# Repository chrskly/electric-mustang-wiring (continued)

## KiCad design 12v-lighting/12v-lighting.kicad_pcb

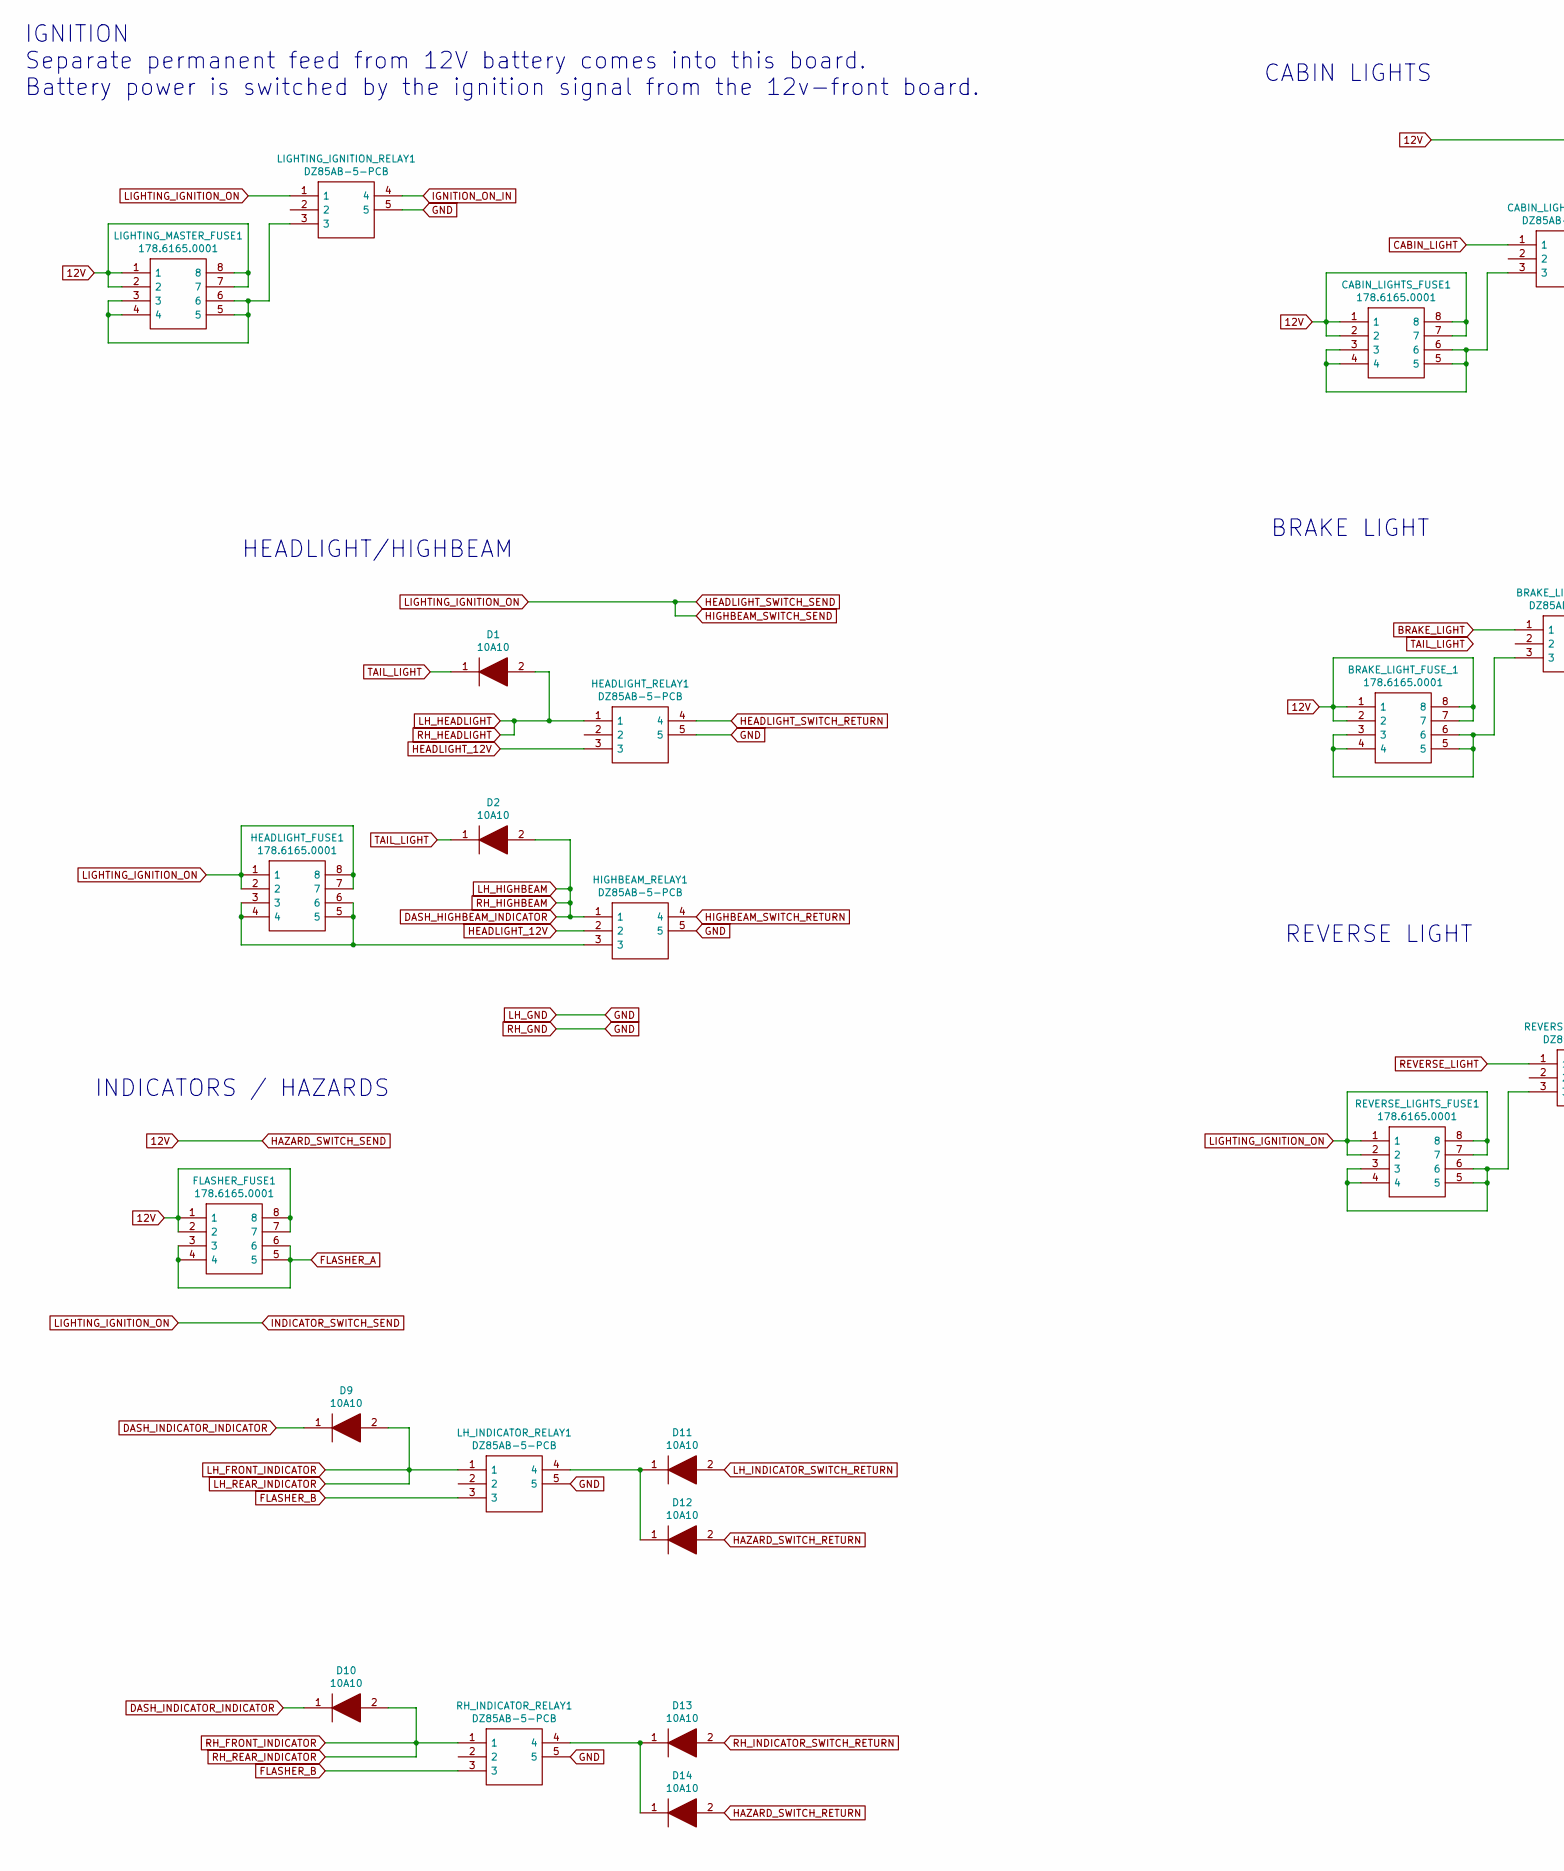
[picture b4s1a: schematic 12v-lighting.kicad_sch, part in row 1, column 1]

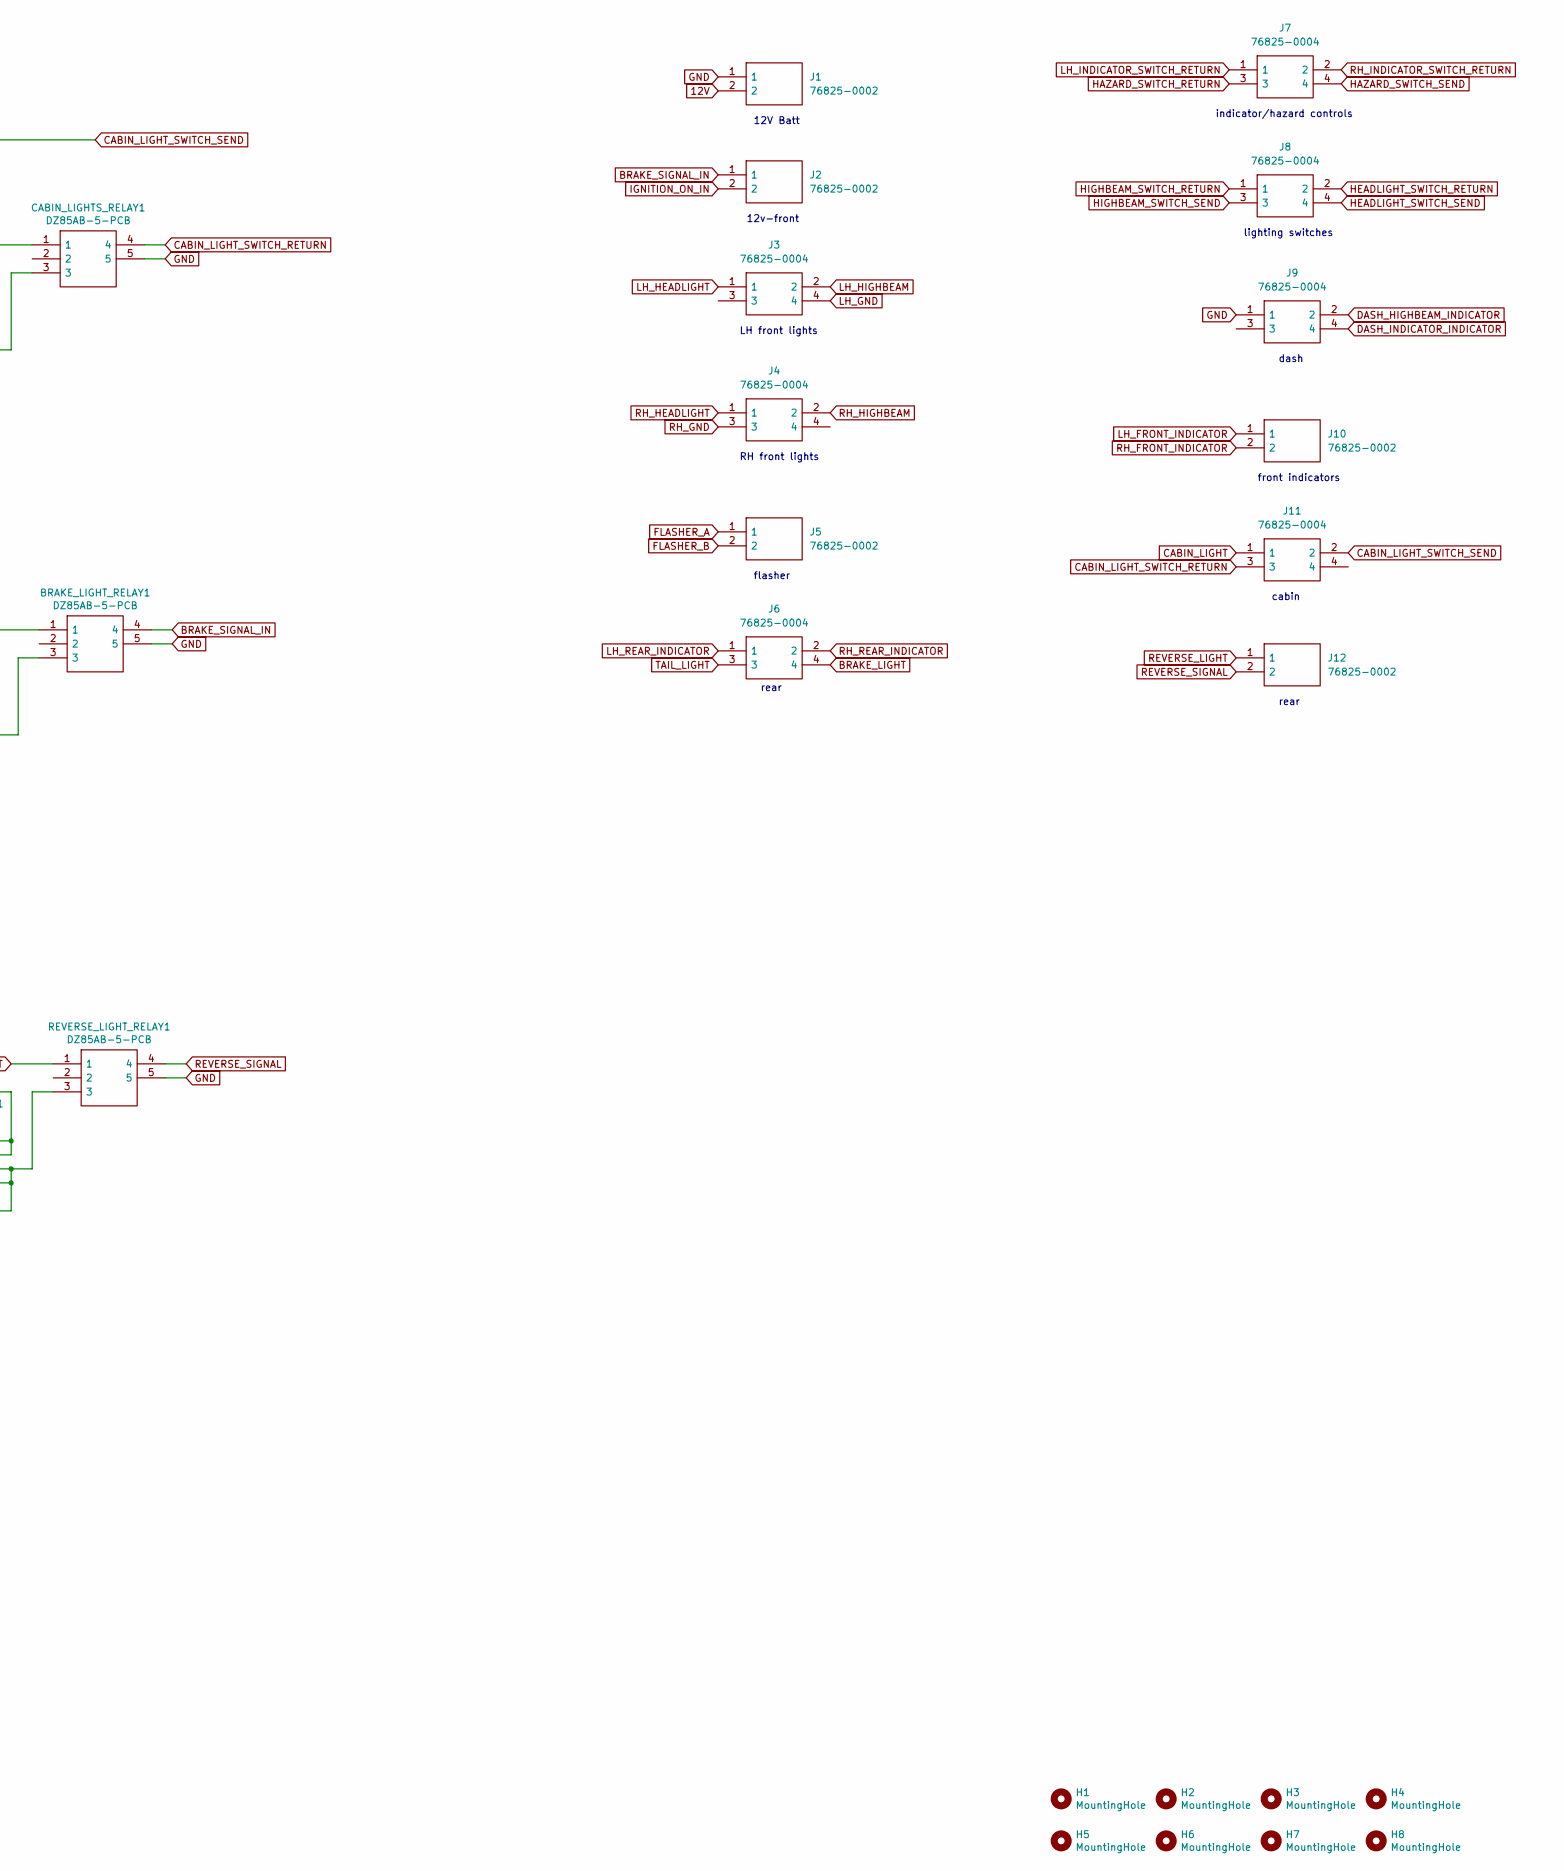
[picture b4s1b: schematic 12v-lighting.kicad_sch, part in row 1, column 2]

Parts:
BRAKE_LIGHT_FUSE_1: 178.6165.0001; 17861650001; Manufacturer_Part_Number 178.6165.0001; Mouser Part Number 576-178.6165.0001
BRAKE_LIGHT_RELAY1: DZ85AB-5-PCB; DZ85AB5PCB; Manufacturer_Part_Number DZ85AB-5-PCB
CABIN_LIGHTS_FUSE1: 178.6165.0001; 17861650001; Manufacturer_Part_Number 178.6165.0001; Mouser Part Number 576-178.6165.0001
CABIN_LIGHTS_RELAY1: DZ85AB-5-PCB; DZ85AB5PCB; Manufacturer_Part_Number DZ85AB-5-PCB
D1, D2, D9, D10, D11, D12, D13, D14: 10A10; D_DO-201AD_P15.24mm_Horizontal; Manufacturer_Part_Number 10A10
FLASHER_FUSE1: 178.6165.0001; 17861650001; Manufacturer_Part_Number 178.6165.0001; Mouser Part Number 576-178.6165.0001
H1, H2, H3, H4, H5, H6, H7, H8: MountingHole; MountingHole_3.2mm_M3
HEADLIGHT_FUSE1: 178.6165.0001; 17861650001; Manufacturer_Part_Number 178.6165.0001; Mouser Part Number 576-178.6165.0001
HEADLIGHT_RELAY1: DZ85AB-5-PCB; DZ85AB5PCB; Manufacturer_Part_Number DZ85AB-5-PCB
HIGHBEAM_RELAY1: DZ85AB-5-PCB; DZ85AB5PCB; Manufacturer_Part_Number DZ85AB-5-PCB
J1, J2, J5, J10, J12: 76825-0002; 768250002; Manufacturer_Part_Number 76825-0002; Mouser Part Number 538-76825-0002
J3, J4, J6, J7, J8, J9, J11: 76825-0004; 768250004; Manufacturer_Part_Number 76825-0004; Mouser Part Number 538-76825-0004
LH_INDICATOR_RELAY1: DZ85AB-5-PCB; DZ85AB5PCB; Manufacturer_Part_Number DZ85AB-5-PCB
LIGHTING_IGNITION_RELAY1: DZ85AB-5-PCB; DZ85AB5PCB; Manufacturer_Part_Number DZ85AB-5-PCB
LIGHTING_MASTER_FUSE1: 178.6165.0001; 17861650001; Manufacturer_Part_Number 178.6165.0001; Mouser Part Number 576-178.6165.0001
REVERSE_LIGHTS_FUSE1: 178.6165.0001; 17861650001; Manufacturer_Part_Number 178.6165.0001; Mouser Part Number 576-178.6165.0001
REVERSE_LIGHT_RELAY1: DZ85AB-5-PCB; DZ85AB5PCB; Manufacturer_Part_Number DZ85AB-5-PCB
RH_INDICATOR_RELAY1: DZ85AB-5-PCB; DZ85AB5PCB; Manufacturer_Part_Number DZ85AB-5-PCB

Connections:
12V: BRAKE_LIGHT_FUSE_1.1, BRAKE_LIGHT_FUSE_1.2, BRAKE_LIGHT_FUSE_1.7, BRAKE_LIGHT_FUSE_1.8, CABIN_LIGHTS_FUSE1.1, CABIN_LIGHTS_FUSE1.2, CABIN_LIGHTS_FUSE1.7, CABIN_LIGHTS_FUSE1.8, FLASHER_FUSE1.1, FLASHER_FUSE1.2, FLASHER_FUSE1.7, FLASHER_FUSE1.8, J1.2, J7.4, J11.2, LIGHTING_MASTER_FUSE1.1, LIGHTING_MASTER_FUSE1.2, LIGHTING_MASTER_FUSE1.7, LIGHTING_MASTER_FUSE1.8
BRAKE_LIGHT: BRAKE_LIGHT_RELAY1.1, J6.4
BRAKE_SIGNAL_IN: BRAKE_LIGHT_RELAY1.4, J2.1
CABIN_LIGHT: CABIN_LIGHTS_RELAY1.1, J11.1
CABIN_LIGHT_SWITCH_RETURN: CABIN_LIGHTS_RELAY1.4, J11.3
DASH_HIGHBEAM_INDICATOR: D2.2, HIGHBEAM_RELAY1.1, J3.2, J4.2, J9.2
DASH_INDICATOR_INDICATOR: D9.1, D10.1, J9.4
FLASHER_A: FLASHER_FUSE1.3, FLASHER_FUSE1.4, FLASHER_FUSE1.5, FLASHER_FUSE1.6, J5.1
FLASHER_B: J5.2, LH_INDICATOR_RELAY1.3, RH_INDICATOR_RELAY1.3
GND: BRAKE_LIGHT_RELAY1.5, CABIN_LIGHTS_RELAY1.5, HEADLIGHT_RELAY1.5, HIGHBEAM_RELAY1.5, J1.1, J3.4, J4.3, J9.1, LH_INDICATOR_RELAY1.5, LIGHTING_IGNITION_RELAY1.5, REVERSE_LIGHT_RELAY1.5, RH_INDICATOR_RELAY1.5
HAZARD_SWITCH_RETURN: D12.2, D14.2, J7.3
HEADLIGHT_12V: HEADLIGHT_RELAY1.3, HIGHBEAM_RELAY1.2
HEADLIGHT_SWITCH_RETURN: HEADLIGHT_RELAY1.4, J8.2
HEADLIGHT_SWITCH_SEND: HEADLIGHT_FUSE1.1, HEADLIGHT_FUSE1.2, HEADLIGHT_FUSE1.7, HEADLIGHT_FUSE1.8, J8.3, J8.4, LIGHTING_IGNITION_RELAY1.1, REVERSE_LIGHTS_FUSE1.1, REVERSE_LIGHTS_FUSE1.2, REVERSE_LIGHTS_FUSE1.7, REVERSE_LIGHTS_FUSE1.8
HIGHBEAM_SWITCH_RETURN: HIGHBEAM_RELAY1.4, J8.1
IGNITION_ON_IN: J2.2, LIGHTING_IGNITION_RELAY1.4
LH_FRONT_INDICATOR: D9.2, J6.1, J10.1, LH_INDICATOR_RELAY1.1
LH_HEADLIGHT: D1.2, HEADLIGHT_RELAY1.1, J3.1, J4.1
LH_INDICATOR_SWITCH_RETURN: D11.2, J7.1
unnamed: BRAKE_LIGHT_FUSE_1.3, BRAKE_LIGHT_FUSE_1.4, BRAKE_LIGHT_FUSE_1.5, BRAKE_LIGHT_FUSE_1.6, BRAKE_LIGHT_RELAY1.3
unnamed: CABIN_LIGHTS_FUSE1.3, CABIN_LIGHTS_FUSE1.4, CABIN_LIGHTS_FUSE1.5, CABIN_LIGHTS_FUSE1.6, CABIN_LIGHTS_RELAY1.3
unnamed: D11.1, D12.1, LH_INDICATOR_RELAY1.4
unnamed: D13.1, D14.1, RH_INDICATOR_RELAY1.4
unnamed: HEADLIGHT_FUSE1.3, HEADLIGHT_FUSE1.4, HEADLIGHT_FUSE1.5, HEADLIGHT_FUSE1.6, HIGHBEAM_RELAY1.3
unnamed: LIGHTING_IGNITION_RELAY1.3, LIGHTING_MASTER_FUSE1.3, LIGHTING_MASTER_FUSE1.4, LIGHTING_MASTER_FUSE1.5, LIGHTING_MASTER_FUSE1.6
unnamed: REVERSE_LIGHTS_FUSE1.3, REVERSE_LIGHTS_FUSE1.4, REVERSE_LIGHTS_FUSE1.5, REVERSE_LIGHTS_FUSE1.6, REVERSE_LIGHT_RELAY1.3
REVERSE_LIGHT: J12.1, REVERSE_LIGHT_RELAY1.1
REVERSE_SIGNAL: J12.2, REVERSE_LIGHT_RELAY1.4
RH_FRONT_INDICATOR: D10.2, J6.2, J10.2, RH_INDICATOR_RELAY1.1
RH_INDICATOR_SWITCH_RETURN: D13.2, J7.2
TAIL_LIGHT: D1.1, D2.1, J6.3

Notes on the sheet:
front indicators
lighting switches
RH front lights
12v-front
dash
LH front lights
REVERSE LIGHT
rear
HEADLIGHT/HIGHBEAM
CABIN LIGHTS
12V Batt
INDICATORS / HAZARDS
cabin
BRAKE LIGHT
flasher
IGNITION Separate permanent feed from 12V battery comes into this board. Battery power is switched by the ignition signal from the 12v-front board.
indicator/hazard controls

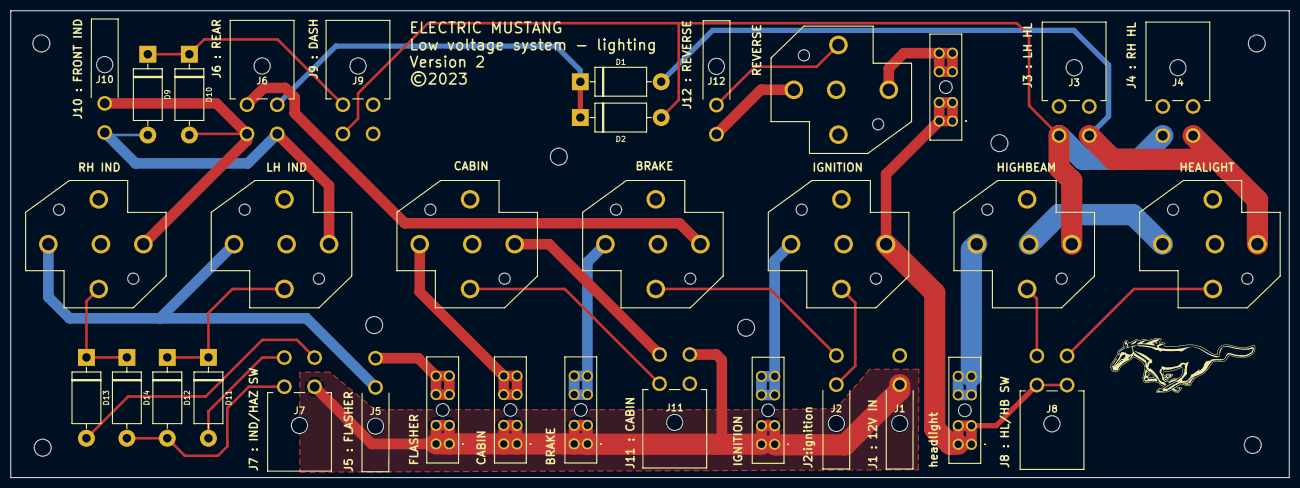
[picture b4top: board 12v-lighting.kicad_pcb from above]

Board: 2 copper layers, 241.0 x 88.0 mm, 42 parts (0 on the bottom side), 31 nets.

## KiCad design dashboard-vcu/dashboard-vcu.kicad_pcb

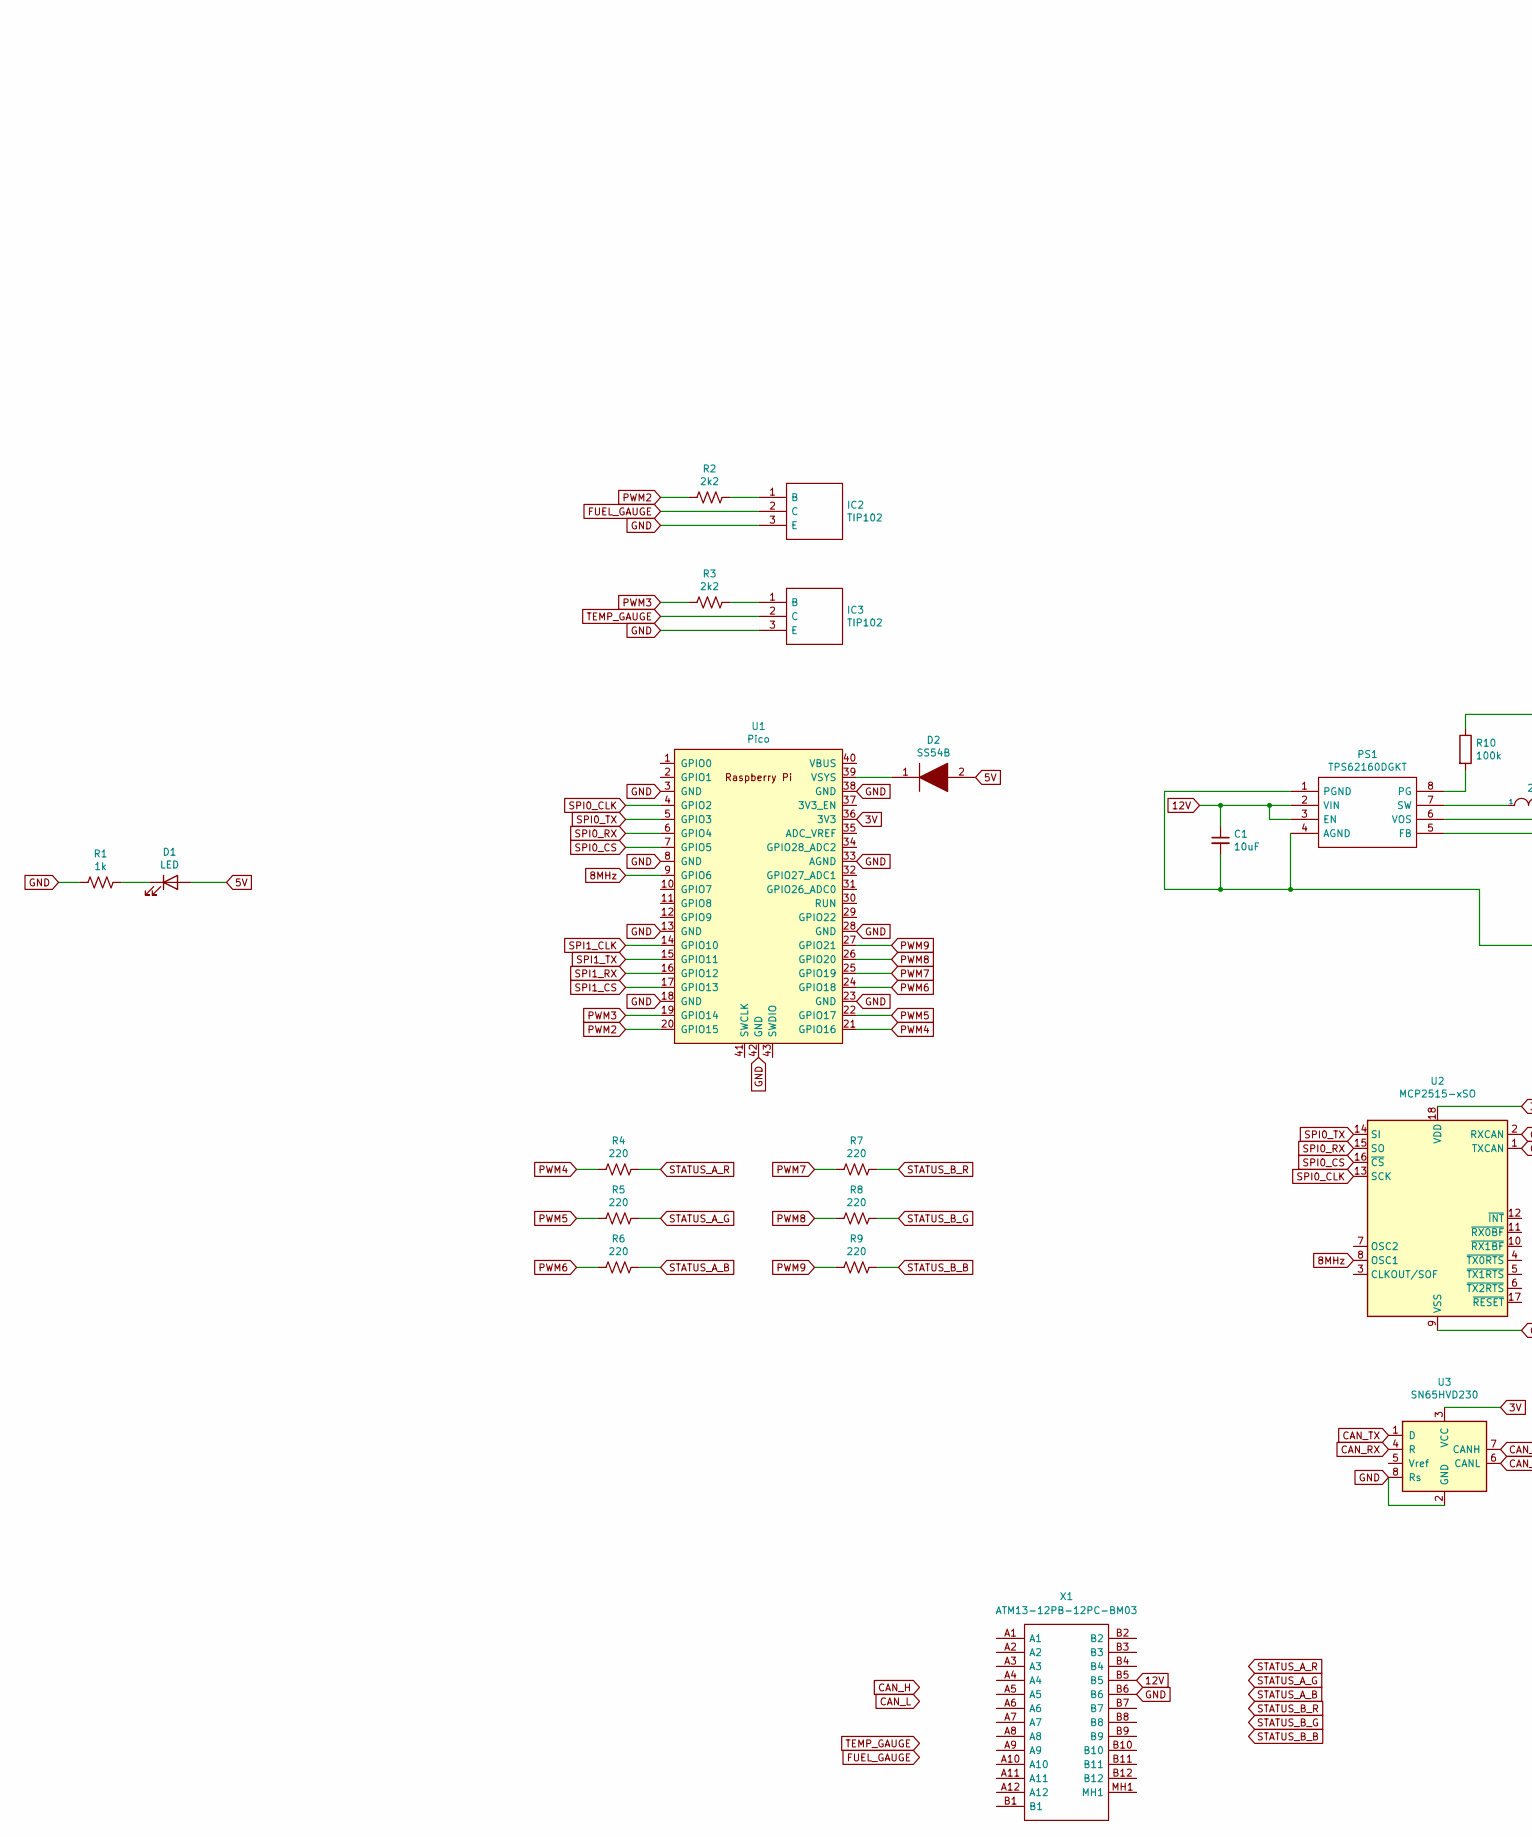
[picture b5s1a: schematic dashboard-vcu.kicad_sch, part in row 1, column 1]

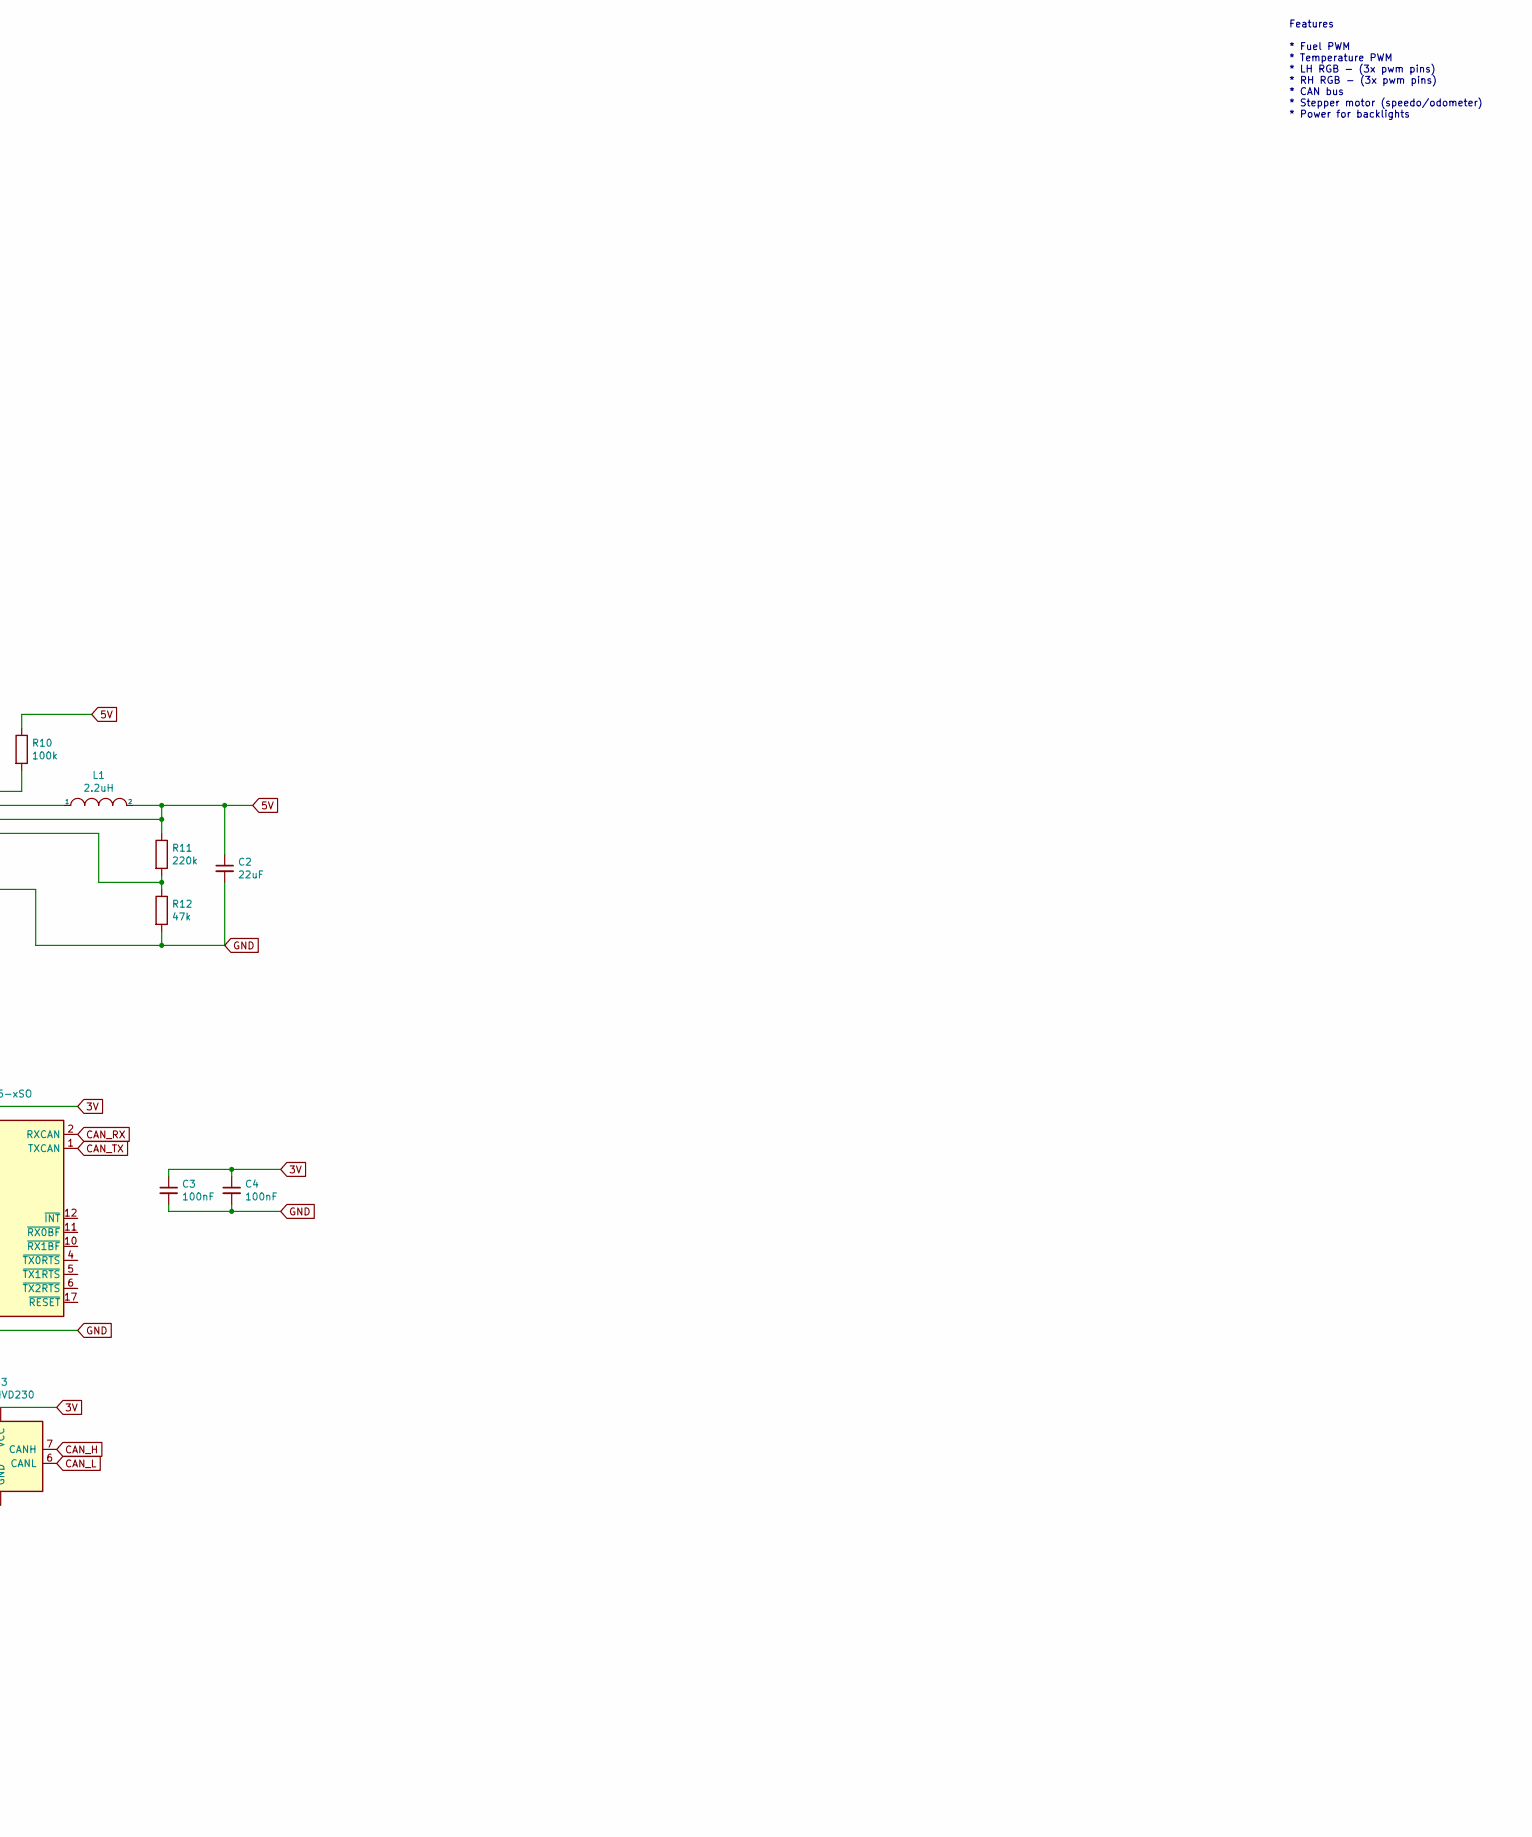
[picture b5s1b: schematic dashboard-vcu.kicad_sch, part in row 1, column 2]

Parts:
C1: 10uF; C_0603_1608Metric
C2: 22uF; C_0805_2012Metric
C3, C4: 100nF; C_0603_1608Metric
D1: LED; LED_0603_1608Metric
D2: SS54B; DIOM5336X244N; Manufacturer_Part_Number SS54B
IC2, IC3: TIP102; TO270P460X1020X2008-3P; Manufacturer_Part_Number TIP102; Mouser Part Number 511-TIP102
L1: 2.2uH; NR6028T220M
PS1: TPS62160DGKT; SOP65P490X110-8N; Manufacturer_Part_Number TPS62160DGKT; Mouser Part Number 595-TPS62160DGKT
R1: 1k; R_0201_0603Metric
R2, R3: 2k2; R_0201_0603Metric
R4, R5, R6, R7, R8, R9: 220; R_0201_0603Metric
R10: 100k; R_0201_0603Metric
R11: 220k; R_0201_0603Metric
R12: 47k; R_0201_0603Metric
U1: Pico; RPi_Pico_SMD_TH
U2: MCP2515-xSO; SOIC-18W_7.5x11.6mm_P1.27mm
U3: SN65HVD230; SOIC-8_3.9x4.9mm_P1.27mm
X1: ATM13-12PB-12PC-BM03; ATM1312PB12PCBM03; Manufacturer_Part_Number ATM13-12PB-12PC-BM03; Mouser Part Number 654-ATM1312B12PCBM03

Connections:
3V: C3.1, C4.1, U1.36 (3V3), U2.18 (VDD), U3.3 (VCC)
5V: C2.1, D1.2 (A), D2.2, L1.2, PS1.6 (VOS), R10.1, R11.1
8MHz: U1.9 (GPIO6), U2.8 (OSC1)
12V: C1.1, PS1.2 (VIN), PS1.3 (EN), X1.B5
CAN_H: U3.7 (CANH)
CAN_L: U3.6 (CANL)
CAN_RX: U2.2 (RXCAN), U3.4 (R)
CAN_TX: U2.1 (TXCAN), U3.1 (D)
FUEL_GAUGE: IC2.2 (C)
GND: C1.2, C2.2, C3.2, C4.2, IC2.3 (E), IC3.3 (E), PS1.1 (PGND), PS1.4 (AGND), R1.2, R12.2, U1.3 (GND), U1.8 (GND), U1.13 (GND), U1.18 (GND), U1.23 (GND), U1.28 (GND), U1.33 (AGND), U1.38 (GND), U1.42 (GND), U2.9 (VSS), U3.2 (GND), U3.8 (Rs), X1.B6
unnamed: D1.1 (K), R1.1
unnamed: D2.1, U1.39 (VSYS)
unnamed: IC2.1 (B), R2.1
unnamed: IC3.1 (B), R3.1
unnamed: L1.1, PS1.7 (SW)
unnamed: PS1.5 (FB), R11.2, R12.1
unnamed: PS1.8 (PG), R10.2
PWM2: R2.2, U1.20 (GPIO15)
PWM3: R3.2, U1.19 (GPIO14)
PWM4: R4.2, U1.21 (GPIO16)
PWM5: R5.2, U1.22 (GPIO17)
PWM6: R6.2, U1.24 (GPIO18)
PWM7: R7.2, U1.25 (GPIO19)
PWM8: R8.2, U1.26 (GPIO20)
PWM9: R9.2, U1.27 (GPIO21)
SPI0_CLK: U1.4 (GPIO2), U2.13 (SCK)
SPI0_CS: U1.7 (GPIO5), U2.16 (~CS)
SPI0_RX: U1.6 (GPIO4), U2.15 (SO)
SPI0_TX: U1.5 (GPIO3), U2.14 (SI)
SPI1_CLK: U1.14 (GPIO10)
SPI1_CS: U1.17 (GPIO13)
SPI1_RX: U1.16 (GPIO12)
SPI1_TX: U1.15 (GPIO11)
STATUS_A_B: R6.1
STATUS_A_G: R5.1
STATUS_A_R: R4.1
STATUS_B_B: R9.1
STATUS_B_G: R8.1
STATUS_B_R: R7.1
TEMP_GAUGE: IC3.2 (C)

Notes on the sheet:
Features * Fuel PWM * Temperature PWM * LH RGB - (3x pwm pins) * RH RGB - (3x pwm pins) * CAN bus * Stepper motor (speedo/odometer) * Power for backlights

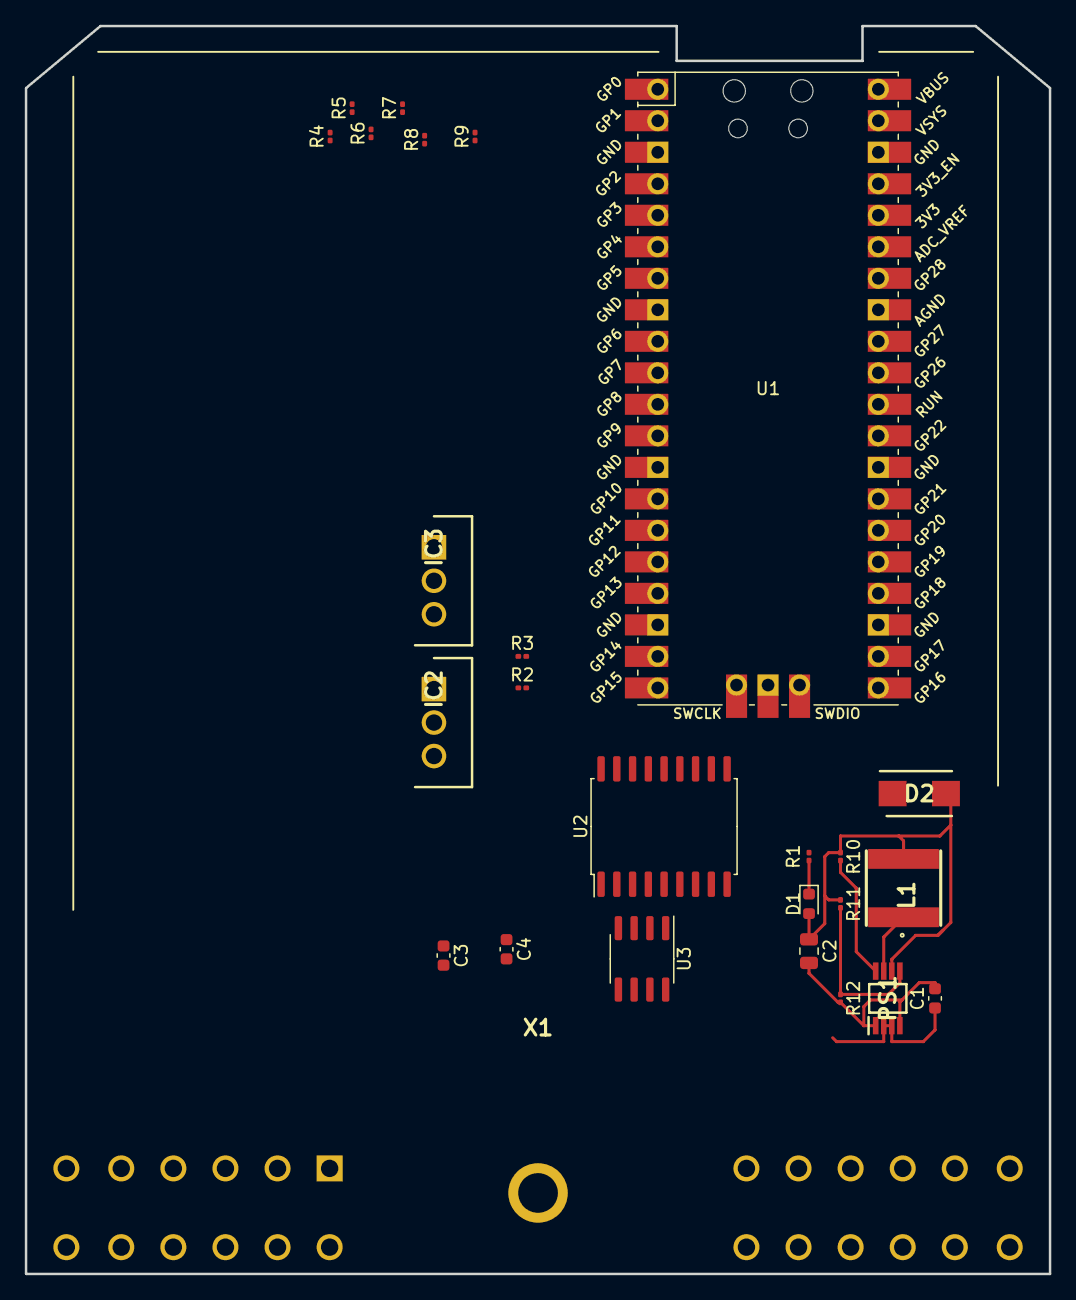
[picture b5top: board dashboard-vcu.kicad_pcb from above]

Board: 2 copper layers, 82.6 x 100.6 mm, 26 parts (0 on the bottom side), 26 nets.

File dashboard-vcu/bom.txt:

Component, Value, Part #, Footprint
U1, rPi Pico
D2, n/a, SS54B, DIOM5336X244N
PS1, n/a, TPS62160DGKT, TPS62160DGKT
C1, 10uF, CL10A106KP8NNNC, 
C2, 22uF, 
L1, 2.2uH, NR6028T2R2N, 
R1, 1k
R2, R3, 2k2,
R4 + R5 + R6 + R7 + R8 + R9, 220, 
R10, 100k, 
R11, 220k,
R12, 47k, 

J1, Molex 39300140

https://datasheet.lcsc.com/lcsc/2004061032_MOLEX-39300140_C4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
https://jlcpcb.com/parts/componentSearch?isSearch=true&searc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
https://www.electronicshub.org/arduino-mcp2515-can-bus-tutorial/
https://www.sparkfun.com/datasheets/DevTools/Arduino/MCP2515.pdf
https://imgur.com/a/pi17C7X

https://www.digikey.be/en/maker/projects/raspberry-pi-pico-r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

https://raspberrypi.github.io/pico-sdk-doxygen/modules.html

Ampseal35, 1.3mm tin 8A, 1.3mm gold 17A

8 circuit molex, high current connections
https://ie.rs-online.com/web/p/pcb-headers/1615968
https://ie.rs-online.com/web/p/pcb-headers/1615961
https://www.molex.com/molex/products/part-detail/pcb_headers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
https://www.molex.com/molex/products/part-detail/crimp_housi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
https://www.molex.com/molex/products/part-detail/crimp_termi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
https://componentsearchengine.com/part-view/172065-0208/Molex

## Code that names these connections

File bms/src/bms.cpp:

/*
 * This file is part of the ev mustang bms project.
 *
 * Copyright (C) 2022 Christian Kelly <chrskly@chrskly.com>
 *
 * This program is free software: you can redistribute it and/or modify
 * it under the terms of the GNU General Public License as published by
 * the Free Software Foundation, either version 3 of the License, or
 * (at your option) any later version.
 *
 * This program is distributed in the hope that it will be useful,
 * but WITHOUT ANY WARRANTY; without even the implied warranty of
 * MERCHANTABILITY or FITNESS FOR A PARTICULAR PURPOSE.  See the
 * GNU General Public License for more details.
 *
 * You should have received a copy of the GNU General Public License
 * along with this program.  If not, see <http://www.gnu.org/licenses/>.
 */

/*------------------------------------------------------------------------------

EV Mustang BMS

Pins
GPIO0  (1)  uart rx  - to ftdi tx
GPIO1  (2)  uart tx  - to ftdi rx
GPIO16 (21) SPI0 RX  - to MISO on both mcp2515 boards (via level converter)
GPIO18 (24) SPI0 SCK - to SCK on both mcp2515 boards (via level converter)
GPIO19 (25) SPI0 TX  - to MOSI on both mcp2515 boards (via level converter)
GPIO17 (22) SPI0 CS0 - to CS on mcp2515 board 0 (via level converter)
SPIO15 (20) SPI0 CS1 - to CS on mcp2515 board 1 (vai level converter)

------------------------------------------------------------------------------*/

using namespace std;

#include <stdio.h>
#include "pico/stdlib.h"
#include "hardware/spi.h"
#include "hardware/uart.h"
#include "hardware/gpio.h"
#include "hardware/clocks.h"
#include "hardware/pll.h"
#include "hardware/watchdog.h"

#include "mcp2515/mcp2515.h"

#include "battery.h"
#include "update.h"
#include "bms.h"
#include "statemachine.h"
#include "comms.h"
#include "led.h"
#include "inputs.h"


struct can_frame rx;

// receive frame
struct can_frame frame;

// error frame
struct can_frame errorFrame;

State state;
StatusLight statusLight;

Battery battery(NUM_PACKS);
MCP2515 mainCAN(SPI_PORT, MAIN_CAN_CS, SPI_MISO, SPI_MOSI, SPI_CLK, 500000);


// Watchdog

struct repeating_timer watchdogKeepaliveTimer;

bool watchdog_keepalive(struct repeating_timer *t) {
    watchdog_update();
    return true;
}

void enable_watchdog_keepalive() {
    add_repeating_timer_ms(5000, watchdog_keepalive, NULL, &watchdogKeepaliveTimer);
}


// Status print

struct repeating_timer statusPrintTimer;

bool status_print(struct repeating_timer *t) {
    battery.print();
    return true;
}

void enable_status_print() {
    add_repeating_timer_ms(5000, status_print, NULL, &statusPrintTimer);
}


/*
 * Update SoC.
 *
 * It's excessive to update this value every time we get a message from the ISA
 * shunt. Just update at a regular interval.
 */

struct repeating_timer socUpdateTimer;

bool update_soc(struct repeating_timer *t) {
    battery.recalculate_soc();
    return true;
}

void enable_update_soc() {
    add_repeating_timer_ms(5000, update_soc, NULL, &socUpdateTimer);
}



int main() {
    stdio_init_all();

    set_sys_clock_khz(80000, true);

    // set up the serial port
    uart_init(UART_ID, BAUD_RATE);
    gpio_set_function(UART_TX_PIN, GPIO_FUNC_UART);
    gpio_set_function(UART_RX_PIN, GPIO_FUNC_UART);

    printf("BMS starting up ...\n");

    state = &state_standby;

    battery.initialise();

    // Set up blinky LED
    gpio_init(PICO_DEFAULT_LED_PIN);
    gpio_set_dir(PICO_DEFAULT_LED_PIN, GPIO_OUT);
    statusLight.led_set_mode(STANDBY);
    enable_led_blink();

    // 8MHz clock for CAN oscillator
    clock_gpio_init(CAN_CLK_PIN, CLOCKS_CLK_GPOUT0_CTRL_AUXSRC_VALUE_CLK_SYS, 10);

    printf("Setting up main CAN port (BITRATE:%d:%d)\n", CAN_500KBPS, MCP_8MHZ);
    mainCAN.reset();
    mainCAN.setBitrate(CAN_500KBPS, MCP_8MHZ);
    mainCAN.setNormalMode();
    printf("Enabling handling of inbound CAN messages on main bus\n");
    enable_handle_main_CAN_messages();

    // Check for unexpected reboot
    if (watchdog_caused_reboot()) {
        printf("Rebooted by Watchdog!\n");
        //errorFame.can_id = ;
        //mainCAN.sendMessage();
        return 0;
    } else {
        printf("Clean boot\n");
    }
    watchdog_enable(100, 1);
    enable_watchdog_keepalive();

    battery.print();
    battery.send_test_message();

    printf("Enabling handling of inbound CAN messages from batteries\n");
    enable_handle_battery_CAN_messages();

    printf("Enabling module polling\n");
    enable_module_polling();

    printf("Enabling status print\n");
    enable_status_print();

    printf("Enable listen for IGNITION_ON signal\n");
    enable_listen_for_ignition_signal();

    printf("Enable listen for CHARGE_ENABLE signal\n");
    enable_listen_for_charge_enable_signal();

    enable_update_soc();

    while(true) {
    }

    return 0;
}

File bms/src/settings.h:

/*
 * This file is part of the ev mustang bms project.
 *
 * Copyright (C) 2022 Christian Kelly <chrskly@chrskly.com>
 *
 * This program is free software: you can redistribute it and/or modify
 * it under the terms of the GNU General Public License as published by
 * the Free Software Foundation, either version 3 of the License, or
 * (at your option) any later version.
 *
 * This program is distributed in the hope that it will be useful,
 * but WITHOUT ANY WARRANTY; without even the implied warranty of
 * MERCHANTABILITY or FITNESS FOR A PARTICULAR PURPOSE.  See the
 * GNU General Public License for more details.
 *
 * You should have received a copy of the GNU General Public License
 * along with this program.  If not, see <http://www.gnu.org/licenses/>.
 */

#ifndef SETTINGS_H
#define SETTINGS_H

#define VERSION 1.0

// Serial port
#define UART_ID      uart0
#define BAUD_RATE   115200
#define UART_TX_PIN      0 // pin 1
#define UART_RX_PIN      1 // pin 2


//#define NUM_PACKS         2                        // The total number of paralleled packs in this battery
#define NUM_PACKS         1
#define CELLS_PER_MODULE 16                        // The number of cells in each module
#define TEMPS_PER_MODULE  4                        // The number of temperature sensors in each module
#define MODULES_PER_PACK  6                        // The number of modules in each pack


#define PACK_ALIVE_TIMEOUT 5                       // If we have not seen an update from the BMS in
                                                   // PACK_ALIVE_TIMEOUT seconds, then mark the pack
                                                   // as dead.

#define SAFE_VOLTAGE_DELTA_BETWEEN_PACKS 0.01      // When closing contactors, the voltage difference between the packs shall not
                                                   // be greater than this voltage, in volts.

//const int CS_PINS[2] = { 20, 15 };               // Chip select pins for the CAN controllers for each battery pack.
//const int CS_PINS[2] = { 15, 15 };
const int CS_PINS[1] = { 15, };

// Outputs
#define CHARGE_INHIBIT_PIN 4                       // Low-side switch to create CHARGE_INHIBIT signal. a.k.a OUT1
#define HEATER_ENABLE_PIN 5                        // Low-side switch to turn on battery heaters. a.k.a. OUT2
const int INHIBIT_CONTACTOR_PINS[2] = { 2, 3 };    // Low-side switch to disallow closing of battery box contactors
#define DRIVE_INHIBIT_PIN 6

// Inputs
#define IGNITION_ENABLE_PIN 10
#define CHARGE_ENABLE_PIN 9
#define IN_1_PIN 11
#define IN_2_PIN 12
#define IN_3_PIN 13
#define IN_4_PIN 14

#define SPI_PORT      spi0

#define SPI_MISO        16 // pin 21
#define SPI_CLK         18 // pin 24
#define SPI_MOSI        19 // pin 25

// mainNet
#define MAIN_CAN_CS     17 // pin 22

#define CAN_CLK_PIN     21 // pin 27

// The capacity of the battery pack
#define BATTERY_CAPACITY_WH 14800   // 7.4kWh usable per pack, x2 packs
#define BATTERY_CAPACITY_AS 187,200 // 26Ah per pack (93,600 As), x2 packs
#define CALCULATE_SOC_FROM 0        // Should we calculate SoC from amp seconds or kWh? 0 = As, else kWh

// Official min pack voltage = 269V. 269 / 6 / 16 = 2.8020833333V
#define CELL_EMPTY_VOLTAGE 2.9

// Official max pack voltage = 398V. 398 / 6 / 16 = 4.1458333333V
#define CELL_FULL_VOLTAGE 4.0

#define CELL_UNDER_TEMPERATURE_FAULT_THRESHOLD 0    // degrees
#define CELL_OVER_TEMPERATURE_WARNING_THRESHOLD 55  // degrees
#define CELL_OVER_TEMPERATURE_FAULT_THRESHOLD 65    // degrees

#define CHARGE_THROTTLE_TEMP_LOW  45                // Start throttling charge current when battery sensors above this temperature
#define CHARGE_THROTTLE_TEMP_HIGH 65                // Top of the throttling scale. Limit current to CHARGE_CURRENT_MIN at and above this temperature
#define CHARGE_CURRENT_MAX 125                      // ~50kw
#define CHARGE_CURRENT_MIN 8                        // ~3.3kw

#define BALANCE_INTERVAL 1200                       // number of seconds between balancing sessions

//// ---- CAN message IDs

#define BMS_LIMITS_MSG_ID 0x351                     // Charge/discharge limits message
#define BMS_SOC_MSG_ID 0x355                        // SoC status message
#define BMS_STATUS_MSG_ID 0x356                     // Status message emitted by the BMS
#define BMS_ALARM_MSG_ID 0x35A                      // Warning message emitted by the BMS

#define CAN_ID_ISA_SHUNT_AH 0x527                   // Message ISA shunt sends which contains Ah data.
#define CAN_ID_ISA_SHUNT_WH 0x528                   // Message ISA shunt sends which contains Wh data.

#endif

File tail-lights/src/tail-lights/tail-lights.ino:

/*
 * This file is part of the ev mustang project.
 *
 * Copyright (C) 2023 Christian Kelly <chrskly@chrskly.com>
 *
 * This program is free software: you can redistribute it and/or modify
 * it under the terms of the GNU General Public License as published by
 * the Free Software Foundation, either version 3 of the License, or
 * (at your option) any later version.
 *
 * This program is distributed in the hope that it will be useful,
 * but WITHOUT ANY WARRANTY; without even the implied warranty of
 * MERCHANTABILITY or FITNESS FOR A PARTICULAR PURPOSE.  See the
 * GNU General Public License for more details.
 *
 * You should have received a copy of the GNU General Public License
 * along with this program.  If not, see <http://www.gnu.org/licenses/>.
 */

#include "state.h"
#include "settings.h"

State state = OFF;

unsigned long flashPoint;
unsigned long previousFlashPoint;

void setup() {

}



void loop() {

/*
    // FLASH overrides everything else
    if ( digitalRead(FLASH_IN_PIN) == 1 ) {
        if ( state != FLASH ) {
            flashPoint = 0;
        }
        do_flash();
    }

    // 
    else if ( digitalRead(BRAKE_IN_PIN) == 1 ) {
        do_brake();
    }

    // Car lights are on, do running lights
    else if ( digitalRead(LIGHTS_ON_IN_PIN) == 1 ) {
        do_lights();
    }

    // Off
    else {
        do_off();
    }
*/

    do_flash();

}
